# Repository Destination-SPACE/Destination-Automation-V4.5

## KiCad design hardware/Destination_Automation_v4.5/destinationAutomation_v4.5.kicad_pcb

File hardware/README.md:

# destination-automation-v4.5

## Getting started

To make it easy for you to get started with GitLab, here's a list of recommended next steps.

Already a pro? Just edit this README.md and make it your own. Want to make it easy? [Use the template at the bottom](#editing-this-readme)!

## Add your files

- [ ] [Create](https://docs.gitlab.com/ee/user/project/repository/web_editor.html#create-a-file) or [upload](https://docs.gitlab.com/ee/user/project/repository/web_editor.html#upload-a-file) files
- [ ] [Add files using the command line](https://docs.gitlab.com/ee/gitlab-basics/add-file.html#add-a-file-using-the-command-line) or push an existing Git repository with the following command:

```
cd existing_repo
git remote add origin https://gitlab.com/Destination-SPACE/ds-team/destination-automation-v4.5.git
git branch -M main
git push -uf origin main
```

## Integrate with your tools

- [ ] [Set up project integrations](https://gitlab.com/Destination-SPACE/ds-team/destination-automation-v4.5/-/settings/integrations)

## Collaborate with your team

- [ ] [Invite team members and collaborators](https://docs.gitlab.com/ee/user/project/members/)
- [ ] [Create a new merge request](https://docs.gitlab.com/ee/user/project/merge_requests/creating_merge_requests.html)
- [ ] [Automatically close issues from merge requests](https://docs.gitlab.com/ee/user/project/issues/managing_issues.html#closing-issues-automatically)
- [ ] [Enable merge request approvals](https://docs.gitlab.com/ee/user/project/merge_requests/approvals/)
- [ ] [Set auto-merge](https://docs.gitlab.com/ee/user/project/merge_requests/merge_when_pipeline_succeeds.html)

## Test and Deploy

Use the built-in continuous integration in GitLab.

- [ ] [Get started with GitLab CI/CD](https://docs.gitlab.com/ee/ci/quick_start/index.html)
- [ ] [Analyze your code for known vulnerabilities with Static Application Security Testing (SAST)](https://docs.gitlab.com/ee/user/application_security/sast/)
- [ ] [Deploy to Kubernetes, Amazon EC2, or Amazon ECS using Auto Deploy](https://docs.gitlab.com/ee/topics/autodevops/requirements.html)
- [ ] [Use pull-based deployments for improved Kubernetes management](https://docs.gitlab.com/ee/user/clusters/agent/)
- [ ] [Set up protected environments](https://docs.gitlab.com/ee/ci/environments/protected_environments.html)

***

# Editing this README

When you're ready to make this README your own, just edit this file and use the handy template below (or feel free to structure it however you want - this is just a starting point!). Thanks to [makeareadme.com](https://www.makeareadme.com/) for this template.

## Suggestions for a good README

Every project is different, so consider which of these sections apply to yours. The sections used in the template are suggestions for most open source projects. Also keep in mind that while a README can be too long and detailed, too long is better than too short. If you think your README is too long, consider utilizing another form of documentation rather than cutting out information.

## Name
Choose a self-explaining name for your project.

## Description
Let people know what your project can do specifically. Provide context and add a link to any reference visitors might be unfamiliar with. A list of Features or a Background subsection can also be added here. If there are alternatives to your project, this is a good place to list differentiating factors.

## Badges
On some READMEs, you may see small images that convey metadata, such as whether or not all the tests are passing for the project. You can use Shields to add some to your README. Many services also have instructions for adding a badge.

## Visuals
Depending on what you are making, it can be a good idea to include screenshots or even a video (you'll frequently see GIFs rather than actual videos). Tools like ttygif can help, but check out Asciinema for a more sophisticated method.

## Installation
Within a particular ecosystem, there may be a common way of installing things, such as using Yarn, NuGet, or Homebrew. However, consider the possibility that whoever is reading your README is a novice and would like more guidance. Listing specific steps helps remove ambiguity and gets people to using your project as quickly as possible. If it only runs in a specific context like a particular programming language version or operating system or has dependencies that have to be installed manually, also add a Requirements subsection.

## Usage
Use examples liberally, and show the expected output if you can. It's helpful to have inline the smallest example of usage that you can demonstrate, while providing links to more sophisticated examples if they are too long to reasonably include in the README.

## Support
Tell people where they can go to for help. It can be any combination of an issue tracker, a chat room, an email address, etc.

## Roadmap
If you have ideas for releases in the future, it is a good idea to list them in the README.

## Contributing
State if you are open to contributions and what your requirements are for accepting them.

For people who want to make changes to your project, it's helpful to have some documentation on how to get started. Perhaps there is a script that they should run or some environment variables that they need to set. Make these steps explicit. These instructions could also be useful to your future self.

You can also document commands to lint the code or run tests. These steps help to ensure high code quality and reduce the likelihood that the changes inadvertently break something. Having instructions for running tests is especially helpful if it requires external setup, such as starting a Selenium server for testing in a browser.

## Authors and acknowledgment
Show your appreciation to those who have contributed to the project.

## License
For open source projects, say how it is licensed.

## Project status
If you have run out of energy or time for your project, put a note at the top of the README saying that development has slowed down or stopped completely. Someone may choose to fork your project or volunteer to step in as a maintainer or owner, allowing your project to keep going. You can also make an explicit request for maintainers.

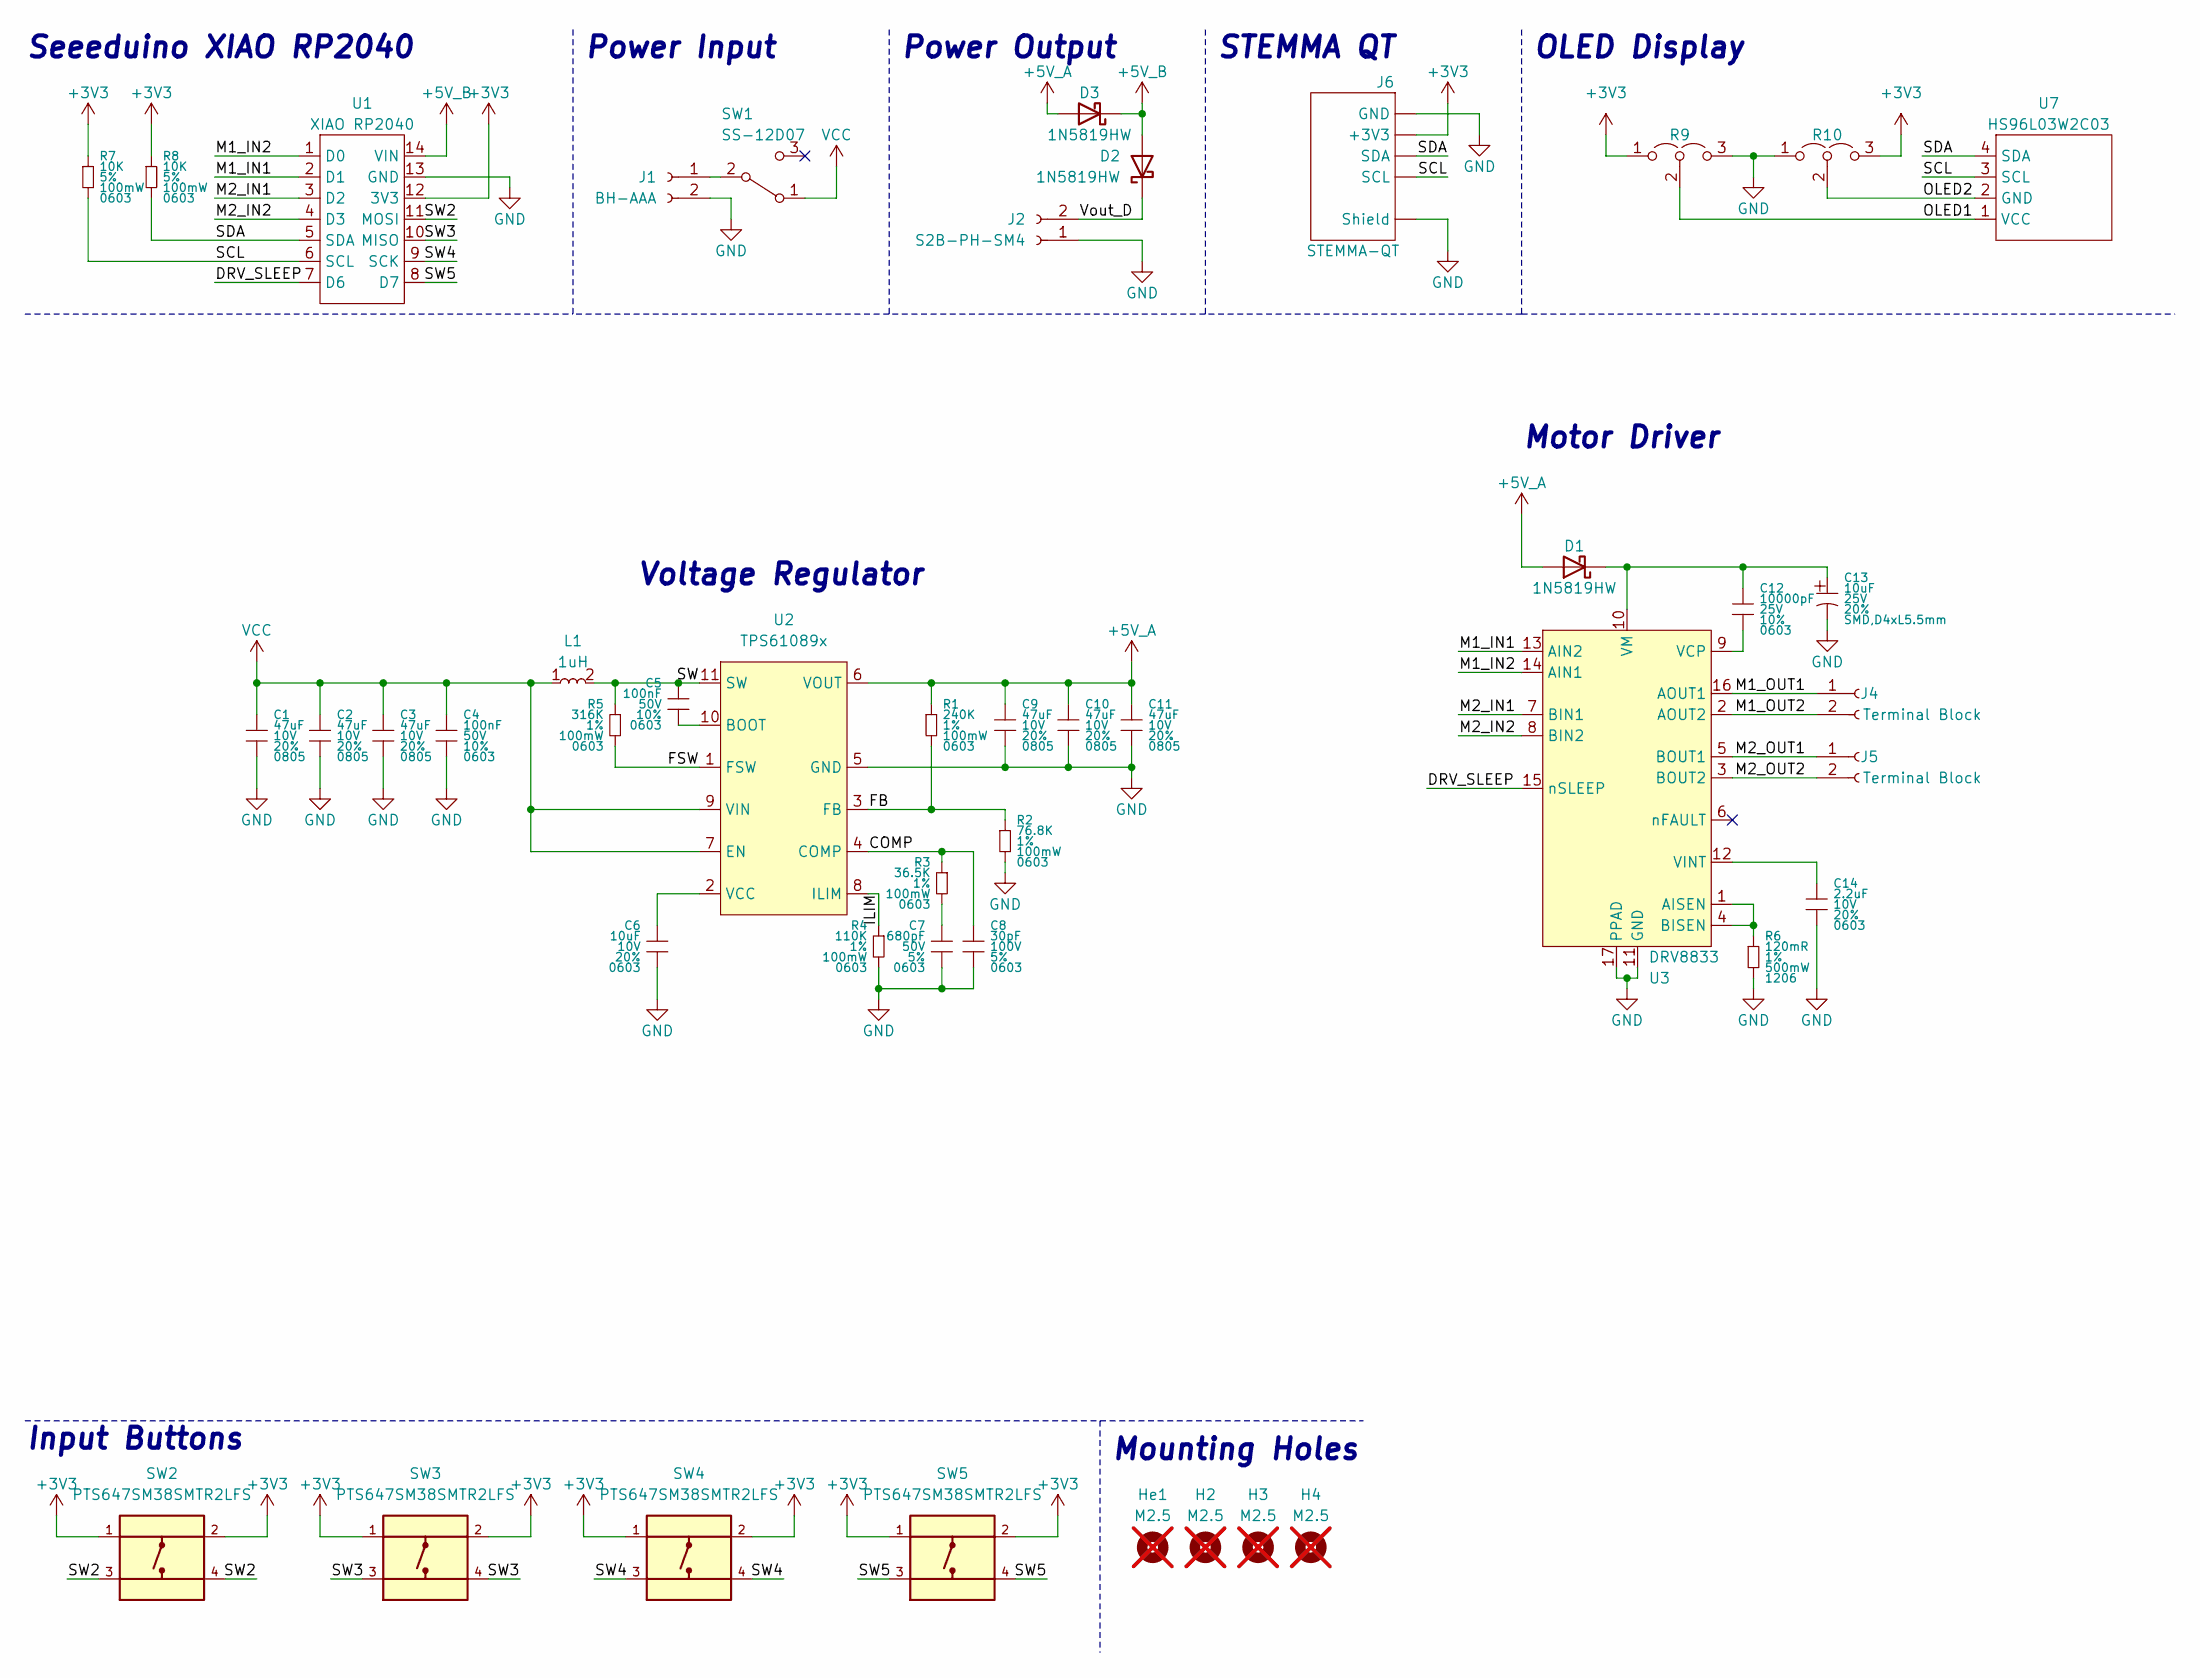
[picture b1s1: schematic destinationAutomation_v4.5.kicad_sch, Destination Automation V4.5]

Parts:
C1, C2, C3, C9, C10, C11: 47uF; CAPC200X125X88L50N; Tolerance 20%; Voltage Rating 10V; mpn KGM21AR51A476MU
C4, C5: 100nF; CAPC160X80X88L35N; Tolerance 10%; Voltage Rating 50V; mpn KGM15AR51H104KT
C6: 10uF; CAPC160X80X88L35N; Tolerance 20%; Voltage Rating 10V; mpn KGM15CR51A106MT
C7: 680pF; CAPC160X80X88L35N; Tolerance 5%; Voltage Rating 50V; mpn KGM15AR71H681JT
C8: 30pF; CAPC160X80X88L35N; Tolerance 5%; Voltage Rating 100V; mpn 06031A300J4T2A
C12: 10000pF; CAPC160X80X88L35N; Tolerance 10%; Voltage Rating 25V; mpn KGM15AR51E103KT
C13: 10uF; CAPAE430X540L180X65N; Tolerance 20%; Voltage Rating 25V; mpn EDK106M025A9BAA
C14: 2.2uF; CAPC160X80X88L35N; Tolerance 20%; Voltage Rating 10V; mpn KGM15BR51A225MT
D1, D2, D3: 1N5819HW; mpn 1N5819HW-7-F
H2, H3, H4: M2.5; M2.54_NPTH; not fitted
He1: M2.5; M2.54_NPTH; not fitted
J1: BH-AAA; BH-AAA-A1AJ024; mpn 2479
J2: S2B-PH-SM4; JST-PH-S2B-SM4-TB; mpn S2B-PH-SM4-TB
J4, J5: Terminal Block; 5mmTerminalBlock; mpn 1935161
J6: STEMMA-QT; JST_SH_SM04B-SRSS-TB; mpn SM04B-SRSS-TB
L1: 1uH; INDC250X200X120L60N; mpn IHHP1008ABER1R0M01
R1: 240K; RESC160X80X55L30N; Tolerance 1%; Power Rating 100mW; mpn CRCW0603240KFKEA
R2: 76.8K; RESC160X80X55L30N; Tolerance 1%; Power Rating 100mW; mpn CRCW060376K8FKEA
R3: 36.5K; RESC160X80X55L30N; Tolerance 1%; Power Rating 100mW; mpn CRCW060336K5FKEAC
R4: 110K; RESC160X80X55L30N; Tolerance 1%; Power Rating 100mW; mpn CRCW0603110KFKEB
R5: 316K; RESC160X80X55L30N; Tolerance 1%; Power Rating 100mW; mpn CRCW0603316KFKEB
R6: 120mR; RESC305X155X65L35_45; Tolerance 1%; Power Rating 500mW; mpn WFC1206R1200FE66
R7, R8: 10K; RESC160X80X55L30N; Tolerance 5%; Power Rating 100mW; mpn CRCW060310K0JNEB
R9, R10: 0R; ResistorJumper-3; mpn CRCW06030000Z0EA
SW1: SS-12D07; SS-12D07-VG_GA_PA; mpn SS-12D07-VG 4 NS GA PA
SW2, SW3, SW4, SW5: PTS647SM38SMTR2LFS; SW_4.5x4.5; mpn PTS 647 SM38 SMTR2 LFS
U1: XIAO RP2040; QtPy; mpn XIAO RP2040
U2: TPS61089x; TPS61089; mpn TPS61089RNRR
U3: DRV8833; DRV8833RTYR; mpn DRV8833RTYR
U7: HS96L03W2C03; mpn HS96L03W2C03

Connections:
+3V3: J6.2 (+3V3), R7.1, R8.1, R9.1 (A), R10.3 (B), SW2.1, SW2.2, SW3.1, SW3.2, SW4.1, SW4.2, SW5.1, SW5.2, U1.12 (3V3)
+5V_A: C9.1, C10.1, C11.1, D1.2 (A), D3.2 (A), R1.1, U2.6 (VOUT)
+5V_B: D2.2 (A), D3.1 (K), U1.14 (VIN)
/COMP: C8.1, R3.1, U2.4 (COMP)
/DRV_SLEEP: U1.7 (D6), U3.15 (nSLEEP)
/FB: R1.2, R2.1, U2.3 (FB)
/FSW: R5.2, U2.1 (FSW)
/ILIM: R4.1, U2.8 (ILIM)
/M1_IN1: U1.2 (D1), U3.13 (AIN2)
/M1_IN2: U1.1 (D0), U3.14 (AIN1)
/M1_OUT1: J4.1, U3.16 (AOUT1)
/M1_OUT2: J4.2, U3.2 (AOUT2)
/M2_IN1: U1.3 (D2), U3.7 (BIN1)
/M2_IN2: U1.4 (D3), U3.8 (BIN2)
/M2_OUT1: J5.1, U3.5 (BOUT1)
/M2_OUT2: J5.2, U3.3 (BOUT2)
/OLED1: R9.2 (C), U7.1 (VCC)
/OLED2: R10.2 (C), U7.2 (GND)
/SCL: J6.4 (SCL), R7.2, U1.6 (SCL), U7.3 (SCL)
/SDA: J6.3 (SDA), R8.2, U1.5 (SDA), U7.4 (SDA)
/SW: C5.1, L1.2, R5.1, U2.11 (SW)
/SW2: SW2.3, SW2.4, U1.11 (MOSI)
/SW3: SW3.3, SW3.4, U1.10 (MISO)
/SW4: SW4.3, SW4.4, U1.9 (SCK)
/SW5: SW5.3, SW5.4, U1.8 (D7)
/Vout_D: D2.1 (K), J2.2
GND: C1.2, C2.2, C3.2, C4.2, C6.2, C7.2, C8.2, C9.2, C10.2, C11.2, C13.2, C14.2, J1.2, J2.1, J6.1 (GND), J6.MP (Shield), R2.2, R4.2, R6.2, R9.3 (B), R10.1 (A), U1.13 (GND), U2.5 (GND), U3.11 (GND), U3.17 (PPAD)
unnamed: C7.1, R3.2
unnamed: C12.1, C13.1, D1.1 (K), U3.10 (VM)
unnamed: J1.1, SW1.2 (B)
unnamed: C5.2, U2.10 (BOOT)
unnamed: C6.1, U2.2 (VCC)
unnamed: R6.1, U3.1 (AISEN), U3.4 (BISEN)
unnamed: C12.2, U3.9 (VCP)
unnamed: C14.1, U3.12 (VINT)
VCC: C1.1, C2.1, C3.1, C4.1, L1.1, SW1.1 (A), U2.7 (EN), U2.9 (VIN)

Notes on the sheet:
Input Buttons
Seeeduino XIAO RP2040
Power Output
Mounting Holes
OLED Display
Power Input
STEMMA QT
Voltage Regulator
Motor Driver

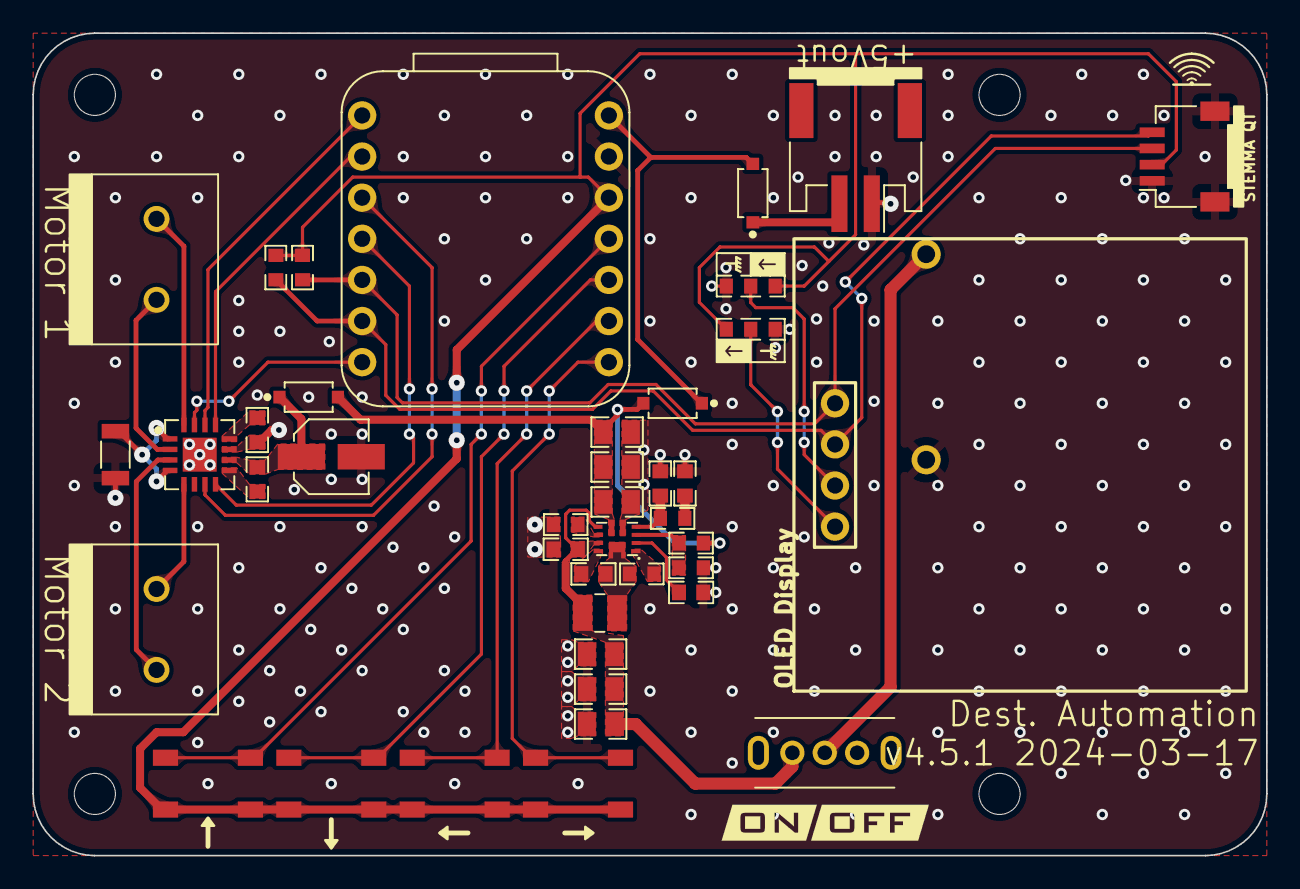
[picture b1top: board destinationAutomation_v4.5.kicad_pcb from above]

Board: 2 copper layers, 76.2 x 50.8 mm, 48 parts (1 on the bottom side), 36 nets.

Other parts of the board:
kibuzzard-652B282B: G***; kibuzzard-652B282B
kibuzzard-652B2846: G***; kibuzzard-652B2846

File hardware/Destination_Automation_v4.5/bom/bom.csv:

Item,Qty,Reference(s),Value,Manufacturer,mpn,populate
1,6,"C1, C2, C3, C9, C10, C11",47uF,KYOCERA AVX,KGM21AR51A476MU,1
2,2,"C4, C5",100nF,KYOCERA AVX,KGM15AR51H104KT,1
3,1,C6,10uF,KYOCERA AVX,KGM15CR51A106MT,1
4,1,C7,680pF,KYOCERA AVX,KGM15AR71H681JT,1
5,1,C8,30pF,KYOCERA AVX,06031A300J4T2A,1
6,1,C12,10000pF,KYOCERA AVX,KGM15AR51E103KT,1
7,1,C13,10uF,KEMET,EDK106M025A9BAA,1
8,1,C14,2.2uF,KYOCERA AVX,KGM15BR51A225MT,1
9,3,"D1, D2, D3",1N5819HW,Diodes Incorporated,1N5819HW-7-F,1
10,1,J1,BH-AAA,Keystone Electronics,2479,0
11,1,J2,S2B-PH-SM4,JST Sales America Inc.,S2B-PH-SM4-TB,1
12,2,"J4, J5",Terminal Block,Phoenix Contact,1935161,0
13,1,J6,STEMMA-QT,JST Sales America Inc.,SM04B-SRSS-TB,1
14,1,L1,1uH,Vishay Dale,IHHP1008ABER1R0M01,1
15,1,R1,240K,Vishay Dale,CRCW0603240KFKEA,1
16,1,R2,76.8K,Vishay Dale,CRCW060376K8FKEA,1
17,1,R3,36.5K,Vishay Dale,CRCW060336K5FKEAC,1
18,1,R4,110K,Vishay Dale,CRCW0603110KFKEB,1
19,1,R5,316K,Vishay Dale,CRCW0603316KFKEB,1
20,1,R6,120mR,Vishay Dale,WFC1206R1200FE66,1
21,1,R7,10K,Vishay Dale,CRCW060310K0JNEB,1
22,1,R8,10K,Vishay Dale,CRCW060310K0JNEB,1
23,2,"R9, R10",0R,Vishay Dale,CRCW06030000Z0EA,1
24,1,SW1,SS-12D07,C&K,SS-12D07-VG 4 NS GA PA,0
25,4,"SW2, SW3, SW4, SW5",PTS647SM38SMTR2LFS,C&K,PTS 647 SM38 SMTR2 LFS,1
26,1,U1,XIAO RP2040,Seeed Studio,XIAO RP2040,0
27,1,U2,TPS61089x,Texas Instruments,TPS61089RNRR,1
28,1,U3,DRV8833, Texas Instruments ,DRV8833RTYR,1
29,1,U7,HS96L03W2C03,SHENZHEN HANSHENG INDUSTRAIL CO.,HS96L03W2C03,0

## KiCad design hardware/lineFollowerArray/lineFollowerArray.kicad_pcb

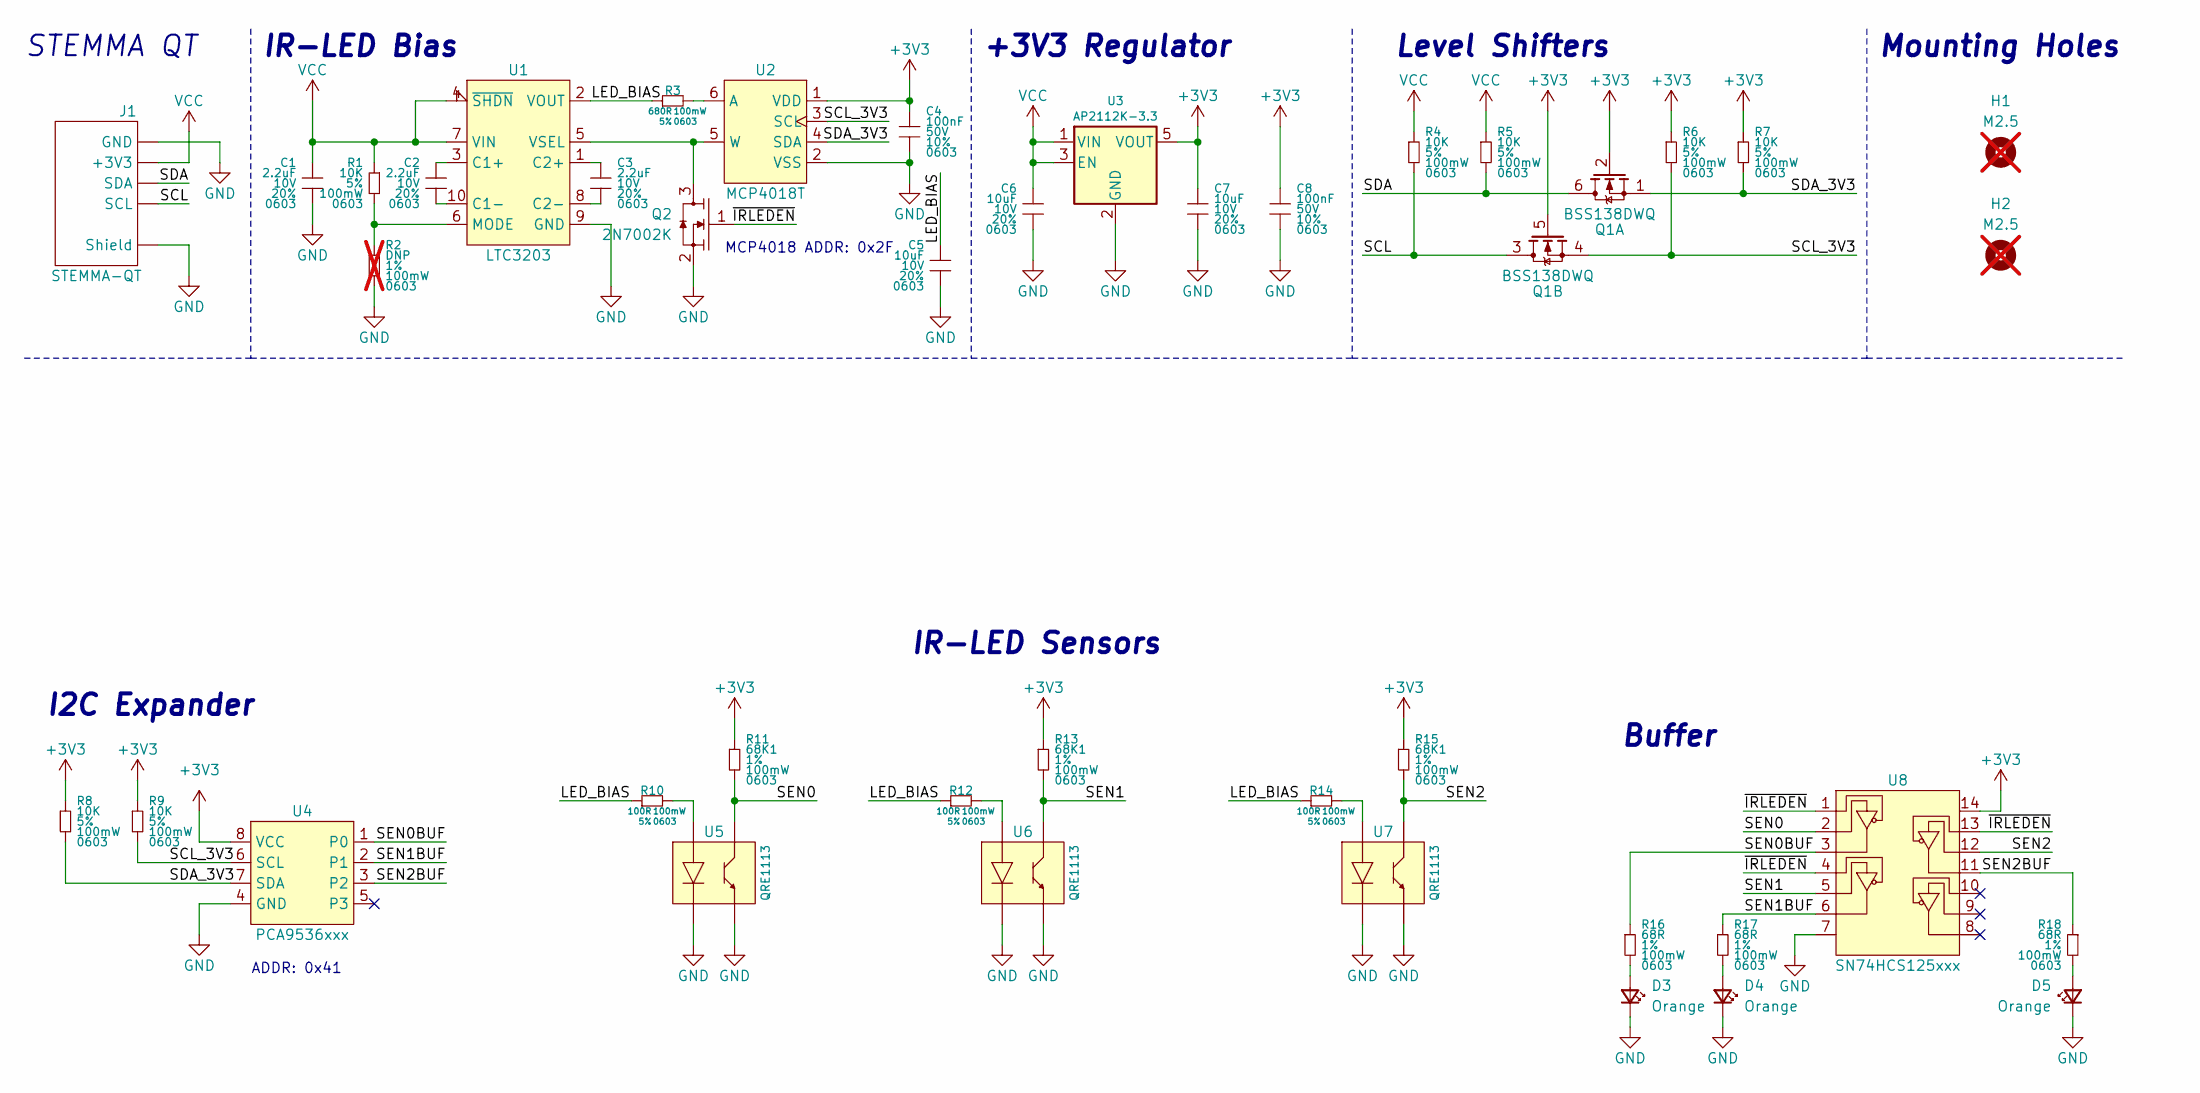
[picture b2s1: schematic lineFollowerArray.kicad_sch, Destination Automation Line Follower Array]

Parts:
C1, C2, C3: 2.2uF; CAPC160X80X88L35N; Tolerance 20%; Voltage Rating 10V; mpn KGM15BR51A225MT
C4, C8: 100nF; CAPC160X80X88L35N; Tolerance 10%; Voltage Rating 50V; mpn KGM15AR51H104KT
C5, C6, C7: 10uF; CAPC160X80X88L35N; Tolerance 20%; Voltage Rating 10V; mpn KGM15CR51A106MT
D3, D4, D5: Orange; LTST-C230KFKT; mpn LTST-C230KFKT
H1, H2: M2.5; M2.54_NPTH; not fitted
J1: STEMMA-QT; JST_SH_SM04B-SRSS-TB; mpn SM04B-SRSS-TB
Q1: BSS138DWQ; SOT23-6P65_210X110L32X20N; mpn BSS138DWQ-7
Q2: 2N7002K; SOT23-3P95_237X111L42X43N; mpn 2N7002KT1G
R1, R4, R5, R6, R7, R8, R9: 10K; RESC160X80X55L30N; Tolerance 5%; Power Rating 100mW; mpn CRCW060310K0JNEB
R2: DNP; RESC160X80X55L30N; Tolerance 1%; Power Rating 100mW; mpn CRCW06030000Z0EA; not fitted
R3: 680R; RESC160X80X55L30N; Tolerance 5%; Power Rating 100mW; mpn CRCW0603680RJNEA
R10, R12, R14: 100R; RESC160X80X55L30N; Tolerance 5%; Power Rating 100mW; mpn CRCW0603100RJNEB
R11, R13, R15: 68K1; RESC160X80X55L30N; Tolerance 1%; Power Rating 100mW; mpn CRCW060368K1FKEA
R16, R17, R18: 68R; RESC160X80X55L30N; Tolerance 1%; Power Rating 100mW; mpn CRCW060368R0FKEA
U1: LTC3203; SON11P50_300X300X85L38X25T238X165N; mpn LTC3203BEDD#PBF
U2: MCP4018T; SOP6P65_200X210X110L28X22N; mpn MCP4018T-103E/LT
U3: AP2112K-3.3; SOT23-5; mpn AP2112K-3.3TRG1
U4: PCA9536xxx; SOP8P65_300X490X110L55X31N; mpn PCA9536DGKR
U5, U6, U7: QRE1113; QRE1113GR; mpn QRE1113GR
U8: SN74HCS125xxx; SOP14P65_500X640X120L62X24N; mpn SN74HCS125PWR

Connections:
+3V3: C4.1, C7.1, C8.1, Q1.2, Q1.5, R6.1, R7.1, R8.1, R9.1, R11.1, R13.1, R15.1, U2.1 (VDD), U3.5 (VOUT), U4.8 (VCC), U8.14 (VCC)
/LED_BIAS: C5.1, R3.1, R10.1, R12.1, R14.1, U1.2 (VOUT)
/SCL: J1.4 (SCL), Q1.3, R4.2
/SCL_3V3: Q1.4, R6.2, R9.2, U2.3 (SCL), U4.6 (SCL)
/SDA: J1.3 (SDA), Q1.6, R5.2
/SDA_3V3: Q1.1, R7.2, R8.2, U2.4 (SDA), U4.7 (SDA)
/SEN0: R11.2, U5.3 (Collector), U8.2 (1A)
/SEN0BUF: R16.1, U4.1 (P0), U8.3 (1Y)
/SEN1: R13.2, U6.3 (Collector), U8.5 (2A)
/SEN1BUF: R17.1, U4.2 (P1), U8.6 (2Y)
/SEN2: R15.2, U7.3 (Collector), U8.12 (4A)
/SEN2BUF: R18.1, U4.3 (P2), U8.11 (4Y)
/~IRLEDEN: Q2.1, U8.1 (1~OE), U8.4 (2~OE), U8.13 (4~OE)
GND: C1.2, C4.2, C5.2, C6.2, C7.2, C8.2, D3.1 (K), D4.1 (K), D5.1 (K), J1.1 (GND), J1.MP (Shield), Q2.2, R2.2, U1.9 (GND), U1.11 (GND), U2.2 (VSS), U3.2 (GND), U4.4 (GND), U5.2 (Cathode), U5.4 (Emitter), U6.2 (Cathode), U6.4 (Emitter), U7.2 (Cathode), U7.4 (Emitter), U8.7 (GND)
unnamed: D3.2 (A), R16.2
unnamed: D4.2 (A), R17.2
unnamed: D5.2 (A), R18.2
unnamed: C2.1, U1.3 (C1+)
unnamed: C2.2, U1.10 (C1-)
unnamed: C3.1, U1.1 (C2+)
unnamed: C3.2, U1.8 (C2-)
unnamed: R1.2, R2.1, U1.6 (MODE)
unnamed: Q2.3, U1.5 (VSEL), U2.5 (W)
unnamed: R3.2, U2.6 (A)
unnamed: R10.2, U5.1 (Anode)
unnamed: R12.2, U6.1 (Anode)
unnamed: R14.2, U7.1 (Anode)
VCC: C1.1, C6.1, J1.2 (+3V3), R1.1, R4.1, R5.1, U1.4 (~SHDN), U1.7 (VIN), U3.1 (VIN), U3.3 (EN)

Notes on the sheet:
Mounting Holes
ADDR: 0x41
Level Shifters
IR-LED Bias
IR-LED Sensors
+3V3 Regulator
MCP4018 ADDR: 0x2F
Buffer
I2C Expander
STEMMA QT

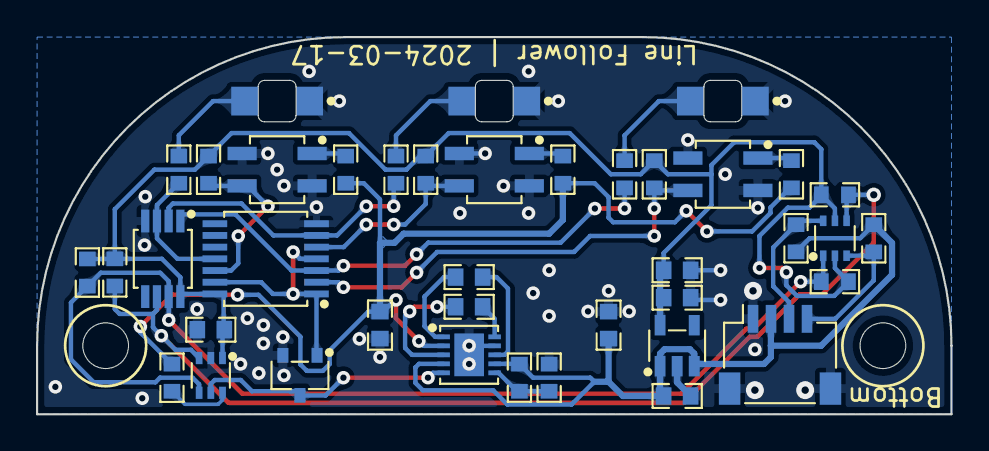
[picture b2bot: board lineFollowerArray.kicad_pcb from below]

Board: 2 copper layers, 50.8 x 21.0 mm, 42 parts (42 on the bottom side), 28 nets.

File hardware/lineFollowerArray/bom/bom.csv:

Item,Qty,Reference(s),Value,Manufacturer,mpn,populate
1,3,"C1, C2, C3",2.2uF,KYOCERA AVX,KGM15BR51A225MT,1
2,2,"C4, C8",100nF,KYOCERA AVX,KGM15AR51H104KT,1
3,3,"C5, C6, C7",10uF,KYOCERA AVX,KGM15CR51A106MT,1
4,3,"D3, D4, D5",Orange,Lite-On Inc.,LTST-C230KFKT,1
5,1,J1,STEMMA-QT,JST Sales America Inc.,SM04B-SRSS-TB,1
6,1,Q1,BSS138DWQ,Diodes Incorporated,BSS138DWQ-7,1
7,1,Q2,2N7002K,onsemi,2N7002KT1G,1
8,1,R1,10K,Vishay Dale,CRCW060310K0JNEB,1
9,1,R3,680R,Vishay Dale,CRCW0603680RJNEA,1
10,6,"R4, R5, R6, R7, R8, R9",10K,Vishay Dale,CRCW060310K0JNEB,1
11,3,"R10, R12, R14",100R,Vishay Dale,CRCW0603100RJNEB,1
12,3,"R11, R13, R15",68K1,Vishay Dale,CRCW060368K1FKEA,1
13,3,"R16, R17, R18",68R,Vishay Dale,CRCW060368R0FKEA,1
14,1,U1,LTC3203,Analog Devices Inc.,LTC3203BEDD#PBF,1
15,1,U2,MCP4018T,Microchip Technology,MCP4018T-103E/LT,1
16,1,U3,AP2112K-3.3,Diodes Incorporated,AP2112K-3.3TRG1,1
17,1,U4,PCA9536xxx,Texas Instruments,PCA9536DGKR,1
18,3,"U5, U6, U7",QRE1113,Onsemi,QRE1113GR,1
19,1,U8,SN74HCS125xxx,Texas Instruments,SN74HCS125PWR,1

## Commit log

2024-12-11 migrated from GitLab
